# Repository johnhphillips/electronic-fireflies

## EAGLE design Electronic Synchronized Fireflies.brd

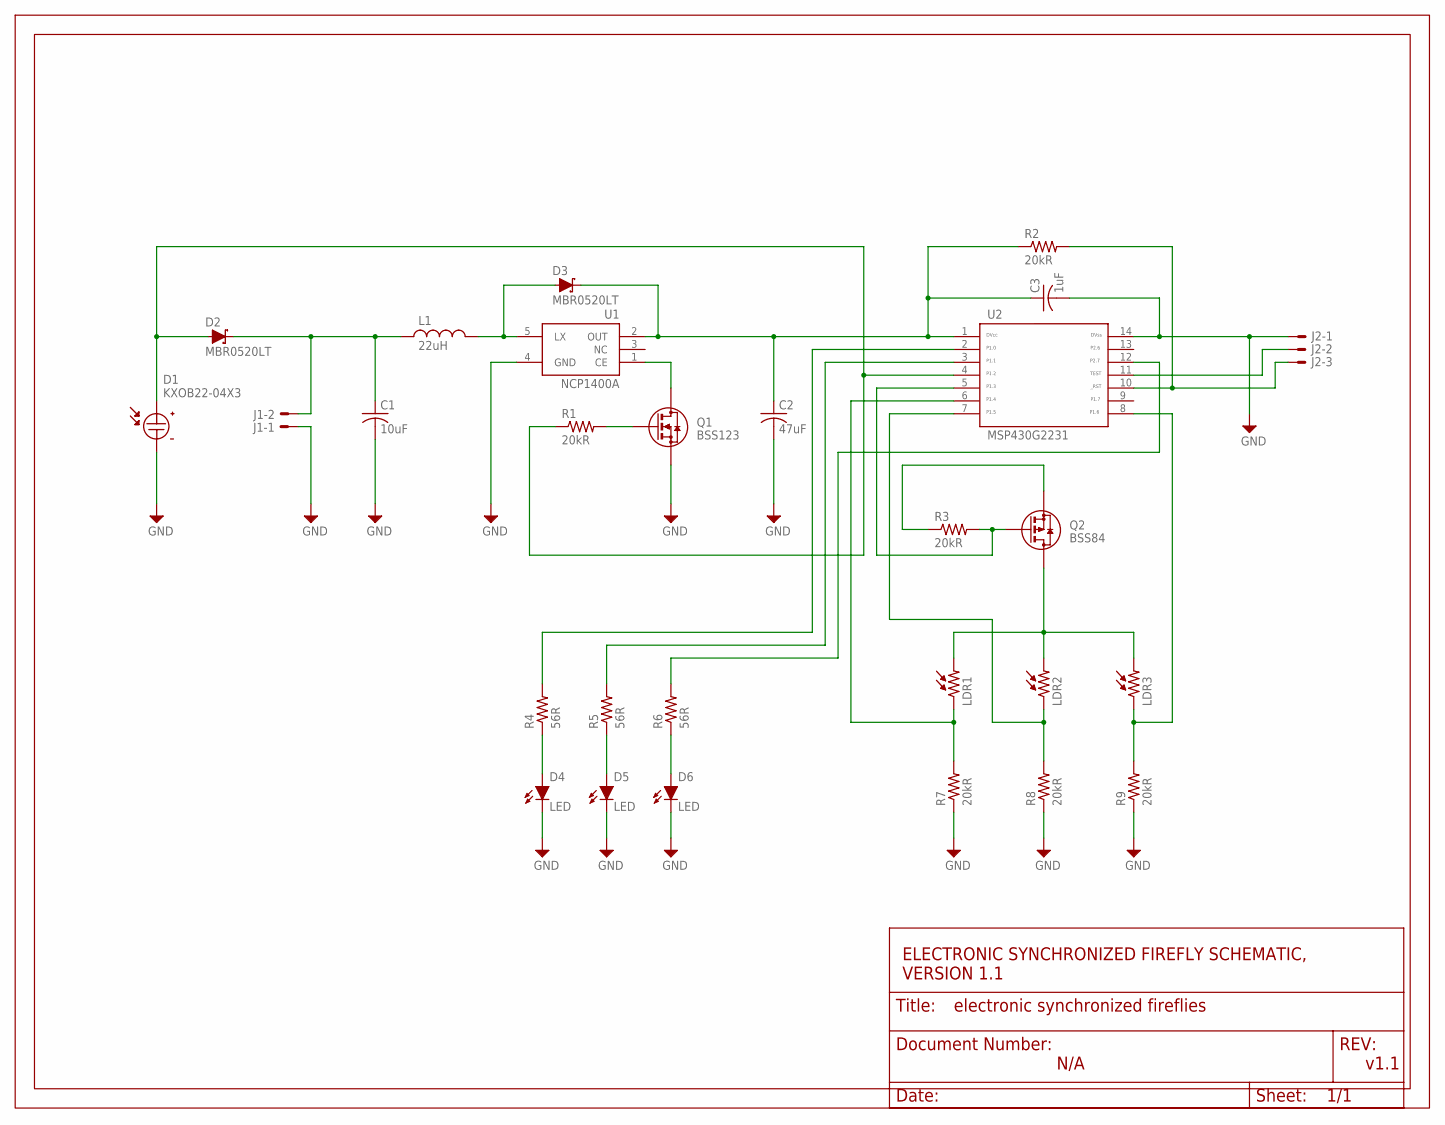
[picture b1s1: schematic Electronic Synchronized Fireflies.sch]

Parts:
C1: 10uF; CAPACITOR_0805
C2: 47uF; CAPACITOR_0805
C3: 1uF; CAPACITOR_0805
D1: KXOB22-04X3
D2, D3: MBR0520LT; SOD123
D4, D5, D6: LED; LED5MMRT
FRAME1: FRAME_A_L
J1: 2WIRE_HEADER
J2: 3WIRE_HEADER
L1: 22uH; INDUCTOR_1007
LDR1, LDR2, LDR3: LDRRTANGLEHOLDER; LED5MMRT
Q1: BSS123; SOT23
Q2: BSS84; SOT23
R1, R2, R3, R7, R8, R9: 20kR; RESISTOR_0805
R4, R5, R6: 56R; RESISTOR_0805
U1: NCP1400A; SOT23-5
U2: MSP430G2231; TSSOP-14
U$1: DOCFIELD

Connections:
GND: C1.2, C2.2, C3.2, D1.P$2 (-), D4.K (C), D5.K (C), D6.K (C), J1.1, J2.1, Q1.3 (D), R7.1, R8.1, R9.1, U1.4 (GND), U2.14
unnamed: C1.1, D2.C, J1.2, L1.P$1 (1)
unnamed: D1.P$1 (+), D2.A, R1.1, U2.4
unnamed: D3.A, L1.P$2 (2), U1.5 (LX)
unnamed: Q2.1 (G), R3.2, U2.5
unnamed: C2.1, C3.1, D3.C, R2.1, U1.2 (OUT), U2.1
unnamed: Q1.2 (S), U1.1 (CE)
unnamed: Q1.1 (G), R1.2
unnamed: LDR1.A (1), R7.2, U2.6
unnamed: J2.3, R2.2, U2.10
unnamed: Q2.2 (S), R3.1
unnamed: J2.2, U2.11
unnamed: LDR1.K (2), LDR2.K (2), LDR3.K (2), Q2.3 (D)
unnamed: LDR2.A (1), R8.2, U2.7
unnamed: LDR3.A (1), R9.2, U2.8
unnamed: R4.2, U2.2
unnamed: R5.2, U2.3
unnamed: R6.2, U2.12
unnamed: D5.A, R5.1
unnamed: D6.A, R6.1
unnamed: D4.A, R4.1

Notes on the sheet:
v1.1
N/A
ELECTRONIC SYNCHRONIZED FIREFLY SCHEMATIC, VERSION 1.1

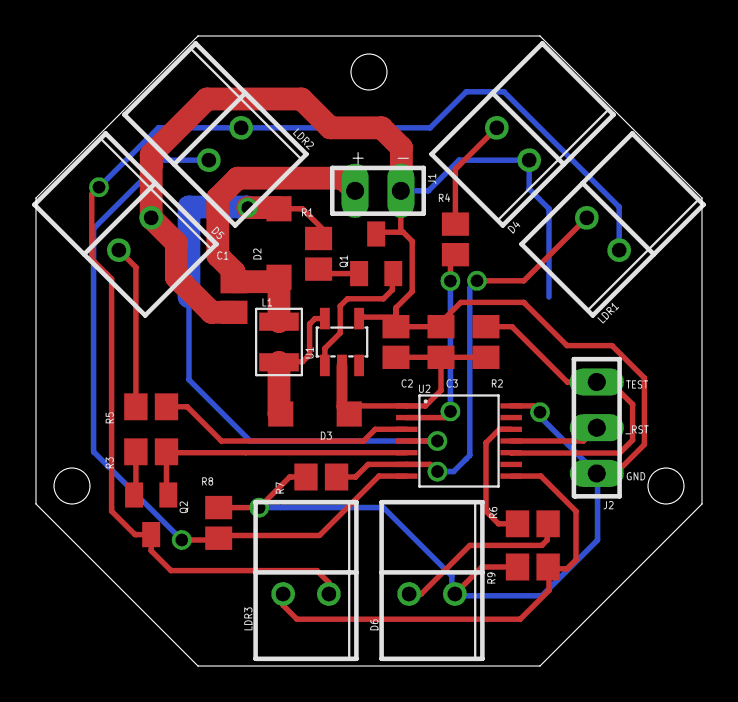
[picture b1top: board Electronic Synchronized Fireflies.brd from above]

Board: 2 copper layers, 37.0 x 35.0 mm, 30 parts (1 on the bottom side), 21 nets.

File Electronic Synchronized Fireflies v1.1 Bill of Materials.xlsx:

Name | Notes |  | Part Number | Source | Unit Cost | On Hand | On Order
B1 | 1.2 V 80 mAh | NiMH 80H w/ tabs | V80H | eBay | 1.65 | 0 | 12
C1 | 10uF output capacitor | 0805 SMT | JMK212BJ106KD-T | Digikey | 0.19 | 5
C2 | 47uF input capacitor | 0805 SMT | JMK212BJ476MG-T | Digikey | 0.77 | 5
D1 | Mono Solar Cell | 22 mm x 7 mm | KXOB22-04X3 | Digikey | 3.3 | 0 | 10
D2 | Blocking diode | SOD-123 | MBR0520LCT-ND | Digikey | 0.36 | 10
D3 | Schottky Power Rectifier | SOD-123 | MBR0520LCT-ND | Digikey | 0.36
L1 | 22 uH Power Inductor | 1007 SMT | CB2518T220K | Digikey | 0.14000000000000001 | 5
IC1 | 1.2 - 3.3V boost convertor | TSOT-23-5 | NCP1400ASN33T1G | Digikey | 0.82 | 5
Q1 | N-Channel Switching MOSFET | SOT-123 | BSS123 | Digikey | 0.24 | 0 | 25
R1 | 20kohm bias resistor | 0805 SMT | RNCP0805FTD20K0 | Digikey | 0.1 | 50*
IC2 | Microcontroller | TSSOP-14 | MSP430G2231IPW14 | Digikey | 1.79 | 5
C3 | 1.0 uF Power capacitor | 0805 SMT | C0805C105K4RACTU | Digikey | 0.12 | 10
Q2 | P-Channel Switching MOSFET | SOT-123 | BSS84 | Digikey | 0.22 | 5
R2 | 20kohm 0.25W | 0805 SMT | RNCP0805FTD20K0 | Digikey | 0.1 | *
R3 | 20kohm 0.25W | 0805 SMT | RNCP0805FTD20K0 | Digikey | 0.1 | *
D4 | 5mm green LED | 5mm | C503B-GCS-CY0C0791 | Digikey | 0.24
D5 | 5mm green LED | 5mm | C503B-GCS-CY0C0791 | Digikey | 0.24
D6 | 5mm green LED | 5mm | C503B-GCS-CY0C0791 | Digikey | 0.24
R4 | 56ohm 0.25W | 0805 SMT | ESR10EZPJ560 | Digikey | 0.1 | 20**
R5 | 56ohm 0.25W | 0805 SMT | ESR10EZPJ561 | Digikey | 0.1 | **
R6 | 56ohm 0.25W | 0805 SMT | ESR10EZPJ562 | Digikey | 0.1 | **
LDR1 | 1Mohm - 20kohm LDR | 5mm | VT935G | Newark | 1.51
LDR2 | 1Mohm - 20kohm LDR | 5mm | VT935G | Newark | 1.51
LDR3 | 1Mohm - 20kohm LDR | 5mm | VT935G | Newark | 1.51
R7 | 20kohm 0.25W | 0805 SMT | RNCP0805FTD20K0 | Digikey | 0.1 | *
R8 | 20kohm 0.25W | 0805 SMT | RNCP0805FTD20K0 | Digikey | 0.1 | *
R9 | 20kohm 0.25W | 0805 SMT | RNCP0805FTD20K0 | Digikey | 0.1 | *
 |  |  |  | PCB Cost | 3.3
 |  |  |  | Total | 19.41

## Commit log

2014-04-02 Initial commit
    v0.1 EECS 398 taken in Fall 2011
2014-04-02 Added power control, PCB improvements
    v0.2
2014-04-02 Connections for panel, battery, PCB improvements
    v0.3 EECS 399 Spring 2012
2014-04-02 Added test points, MOSFET switch, 0R resistors.
    v1.0 First run PCB
2014-04-02 Reduced number of parts, LDRs to phototransistors
    v1.1 Changed from 4 pairs of LEDs and LDRs to three pairs of LEDs and
    phototransistors. Replaced power transistor with MOSFET and solar cell
    connection with surface mount photocell.
2014-04-03 Updated board / schematic / library
    Smaller PCB footprint, added frames to board layout.
2014-04-03 Fixed battery lines covered by solar cell. Added labels.
2014-04-03 Added drill holes, ground plane, octagon board
2014-04-03 Added detail to document fields (Schematic/PCB)
2014-08-25 Move back to LDR setup
2014-12-11 Added BOM
